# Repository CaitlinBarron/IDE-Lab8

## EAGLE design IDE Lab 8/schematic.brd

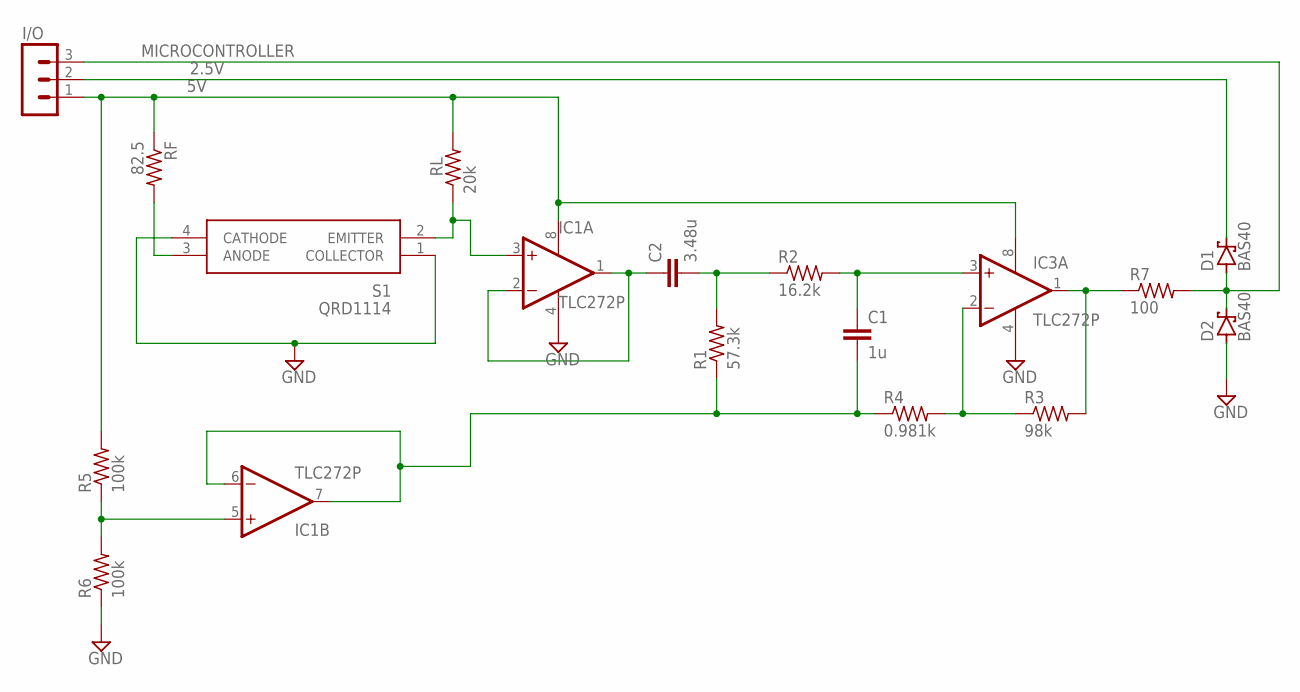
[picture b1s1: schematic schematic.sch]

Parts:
C1: 1u; C0402
C2: 3.48u; C0402
D1, D2: BAS40; SOT23
I/O: MA03-1
IC1, IC3: TLC272P; DIL08
R1: 57.3k; M0805
R2: 16.2k; M0805
R3: 98k; M0805
R4: 0.981k; M0805
R5: 100k; M0805
R6: 100k; 0204/5
R7: 100; M0805
RF: 82.5; M0805
RL: 20k; M0805
S1: QRD1114; CUSTOM_4L

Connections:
2.5V: D1.3 (C), I/O.2
5V: I/O.1, IC1.8 (V+), IC3.8 (V+), R5.2, RF.1, RL.2
GND: D2.1 (A), IC1.4 (V-), IC3.4 (V-), R6.1, S1.1 (COLLECTOR), S1.4 (CATHODE)
MICROCONTROLLER: D1.1 (A), D2.3 (C), I/O.3, R7.2
unnamed: RF.2, S1.3 (ANODE)
unnamed: IC1.3 (+IN), RL.1, S1.2 (EMITTER)
unnamed: C2.1, IC1.1 (OUT), IC1.2 (-IN)
unnamed: IC1.5 (+IN), R5.1, R6.2
unnamed: C2.2, R1.2, R2.1
unnamed: C1.1, IC3.3 (+IN), R2.2
unnamed: C1.2, IC1.6 (-IN), IC1.7 (OUT), R1.1, R4.1
unnamed: IC3.2 (-IN), R3.1, R4.2
unnamed: IC3.1 (OUT), R3.2, R7.1

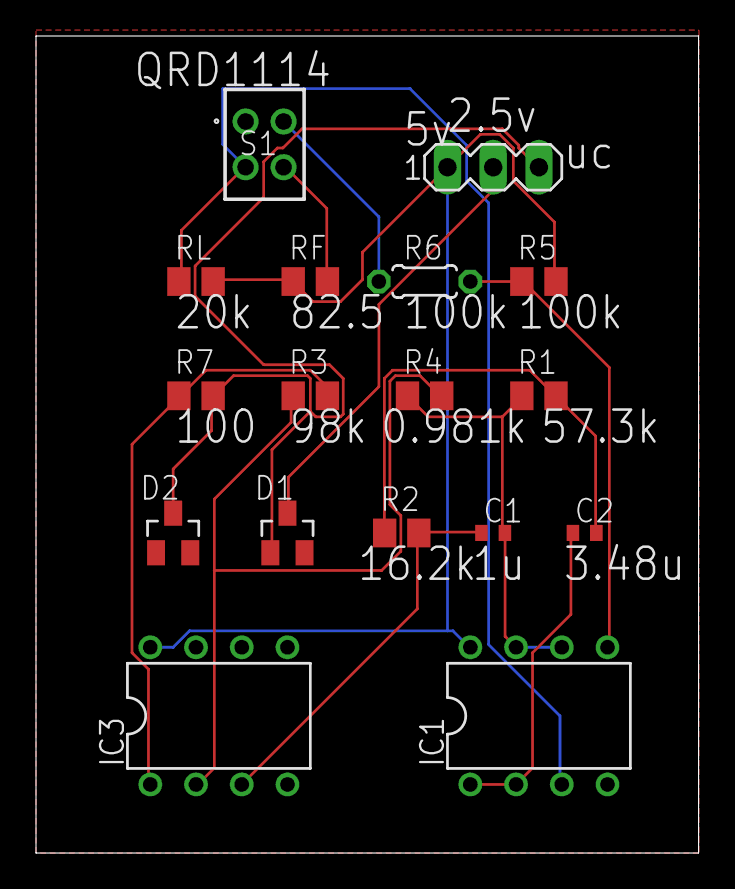
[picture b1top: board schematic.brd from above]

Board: 2 copper layers, 36.8 x 45.4 mm, 17 parts (0 on the bottom side), 13 nets.

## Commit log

2019-04-15 added screenshots, PSPICE, and EAGLE
